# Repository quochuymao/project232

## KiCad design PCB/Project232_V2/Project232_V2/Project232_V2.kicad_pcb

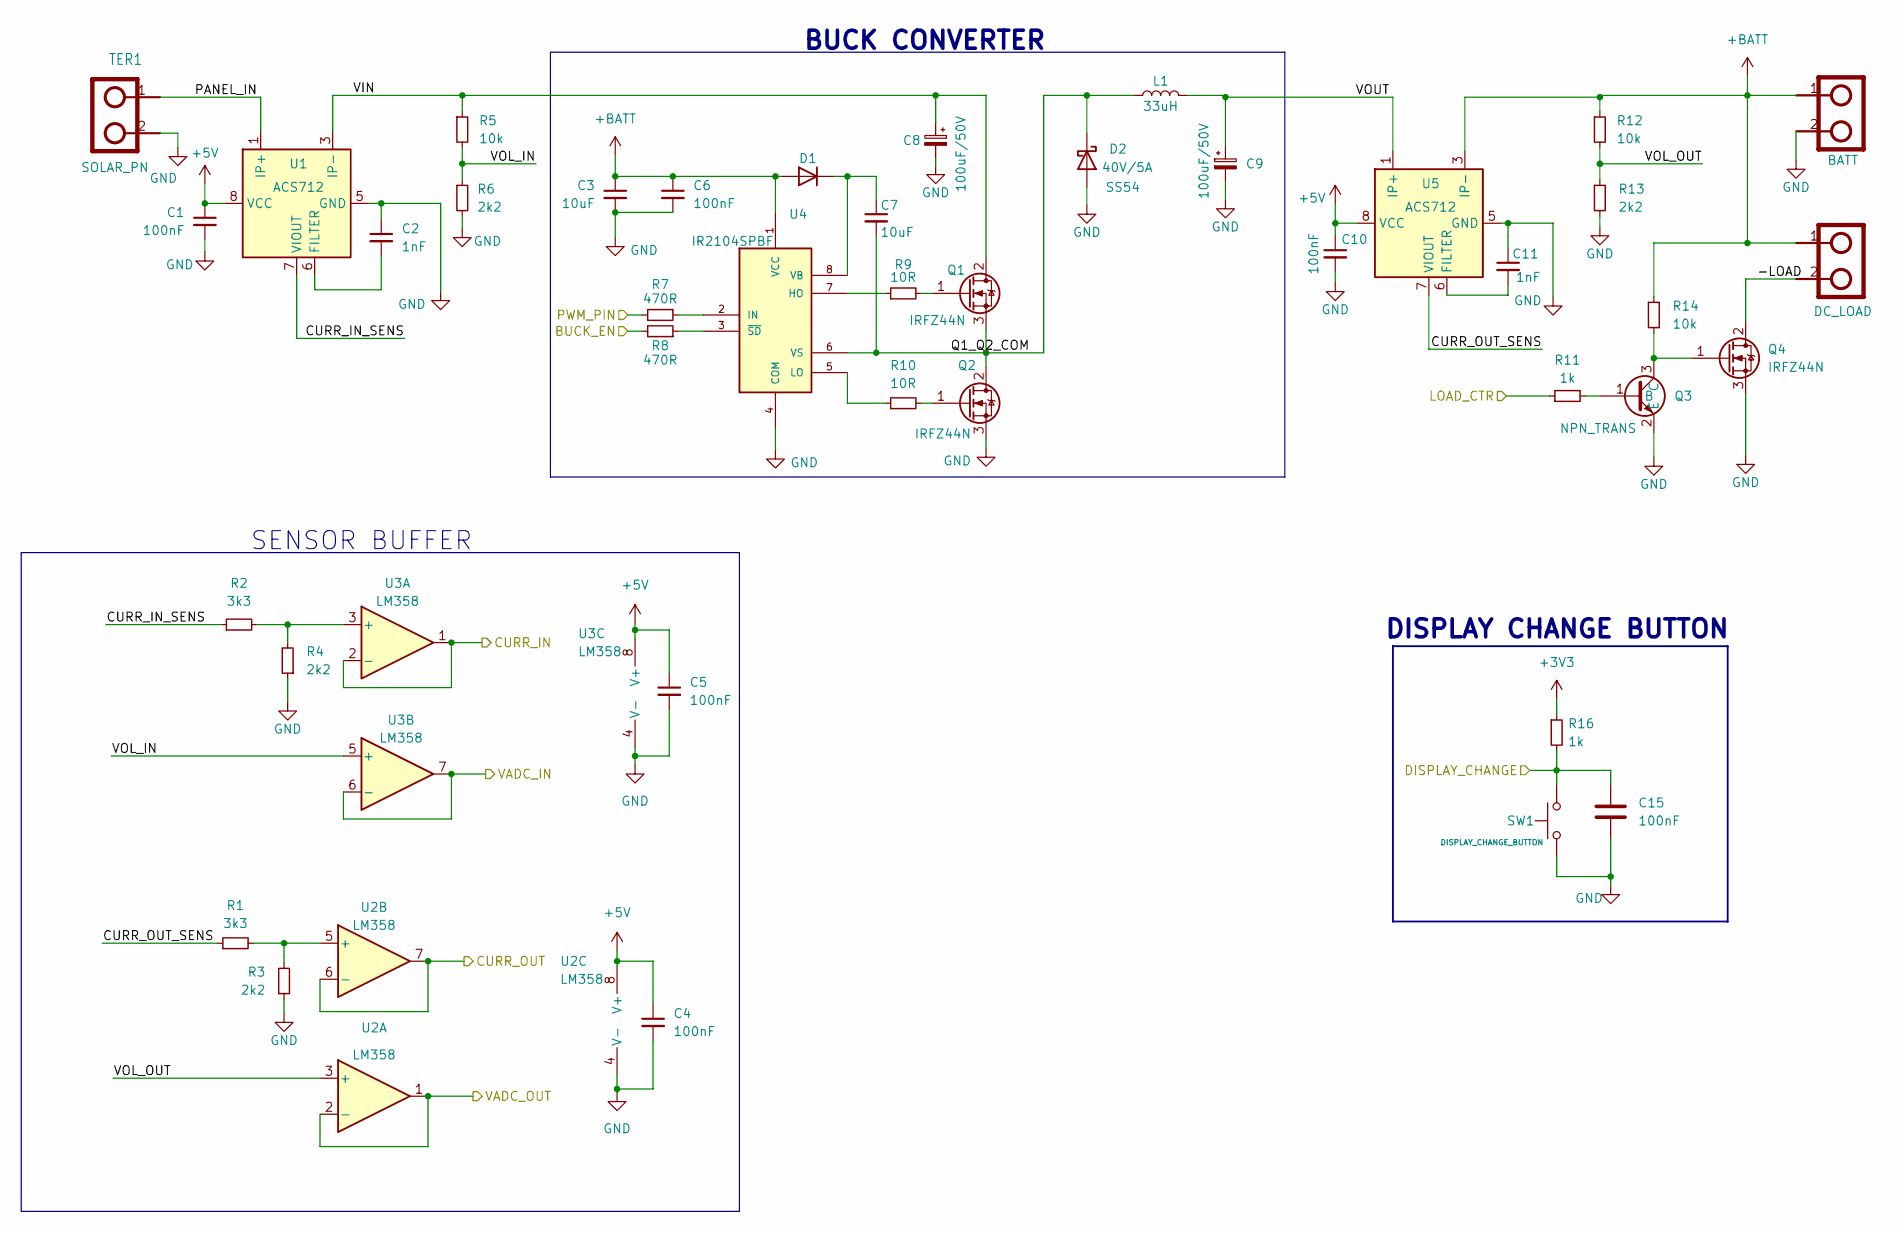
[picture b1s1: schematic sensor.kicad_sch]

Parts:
C1, C4, C5, C6, C10, C15: 100nF; C_0805_2012Metric
C2, C11: 1nF; C_0805_2012Metric
C3, C7: 10uF; C_0805_2012Metric
C8, C9: 100uF/50V; CP_Elec_8x10.5
D1: 1N5819W; D_SOD-123
D2: 40V/5A; D_SMC
L1: 33uH; Inductor_33uH_5A_THT
Q1, Q2, Q4: IRFZ44N; TO-220-3_Vertical
Q3: NPN_TRANS; SOT-23
R1, R2: 3k3; R_0603_1608Metric
R3, R4, R6, R13: 2k2; R_0603_1608Metric
R5, R12, R14: 10k; R_0603_1608Metric
R7, R8: 470R; R_0603_1608Metric
R9, R10: 10R; R_0603_1608Metric
R11, R16: 1k; R_0603_1608Metric
SW1: DISPLAY_CHANGE_BUTTON; Button_3x6_SMD
TER1: SOLAR_PN; TerminalBlock_bornier-2_P5.08mm
TER2: BATT; TerminalBlock_bornier-2_P5.08mm
TER3: DC_LOAD; TerminalBlock_bornier-2_P5.08mm
U1, U5: ACS712; SOIC-8_3.9x4.9mm_P1.27mm
U2, U3: LM358; SOIC-8_3.9x4.9mm_P1.27mm
U4: IR2104SPBF; SOIC127P600X175-8N; MPN IR2104SPBF

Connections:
+3V3: R16.1; also elsewhere on the board
+5V: C1.1, C4.1, C5.1, C10.1, U1.8 (VCC), U2.8 (V+), U3.8 (V+), U5.8 (VCC); also elsewhere on the board
+BATT: C3.1, C6.1, D1.2 (A), R12.1, R14.1, TER2.1, TER3.1, U4.1 (VCC), U5.3 (IP-), U5.4 (IP-); also elsewhere on the board
/MCU/BUCK_EN: R8.2; also elsewhere on the board
/MCU/CURR_IN: U3.1, U3.2 (-); also elsewhere on the board
/MCU/CURR_OUT: U2.6 (-), U2.7; also elsewhere on the board
/MCU/DISPLAY_CHANGE: C15.1, R16.2, SW1.1; also elsewhere on the board
/MCU/LOAD_CTR: R11.1; also elsewhere on the board
/MCU/PWM_PIN: R7.2; also elsewhere on the board
/MCU/VADC_IN: U3.6 (-), U3.7; also elsewhere on the board
/MCU/VADC_OUT: U2.1, U2.2 (-); also elsewhere on the board
/Sensor/-LOAD: Q4.2 (D), TER3.2
/Sensor/CURR_IN_SENS: R2.1, U1.7 (VIOUT)
/Sensor/CURR_OUT_SENS: R1.1, U5.7 (VIOUT)
/Sensor/PANEL_IN: TER1.1, U1.1 (IP+), U1.2 (IP+)
/Sensor/Q1_Q2_COM: C7.2, D2.1 (K), L1.1, Q1.3 (S), Q2.2 (D), U4.6 (VS)
/Sensor/VIN: C8.1, Q1.2 (D), R5.1, U1.3 (IP-), U1.4 (IP-)
/Sensor/VOL_IN: R5.2, R6.1, U3.5 (+)
/Sensor/VOL_OUT: R12.2, R13.1, U2.3 (+)
/Sensor/VOUT: C9.1, L1.2, U5.1 (IP+), U5.2 (IP+)
GND: C1.2, C2.1, C3.2, C4.2, C5.2, C6.2, C8.2, C9.2, C10.2, C11.1, C15.2, D2.2 (A), Q2.3 (S), Q3.2 (E), Q4.3 (S), R3.1, R4.1, R6.2, R13.2, SW1.2, TER1.2, TER2.2, U1.5 (GND), U2.4 (V-), U3.4 (V-), U4.4 (COM), U5.5 (GND); also elsewhere on the board
unnamed: C7.1, D1.1 (K), U4.8 (VB)
unnamed: Q1.1 (G), R9.2
unnamed: Q2.1 (G), R10.2
unnamed: Q3.1 (B), R11.2
unnamed: Q3.3 (C), Q4.1 (G), R14.2
unnamed: C2.2, U1.6 (FILTER)
unnamed: R1.2, R3.2, U2.5 (+)
unnamed: R2.2, R4.2, U3.3 (+)
unnamed: R9.1, U4.7 (HO)
unnamed: R7.1, U4.2 (IN)
unnamed: R10.1, U4.5 (LO)
unnamed: R8.1, U4.3 (~SD)
unnamed: C11.2, U5.6 (FILTER)

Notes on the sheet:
BUCK CONVERTER
SENSOR BUFFER
DISPLAY CHANGE BUTTON

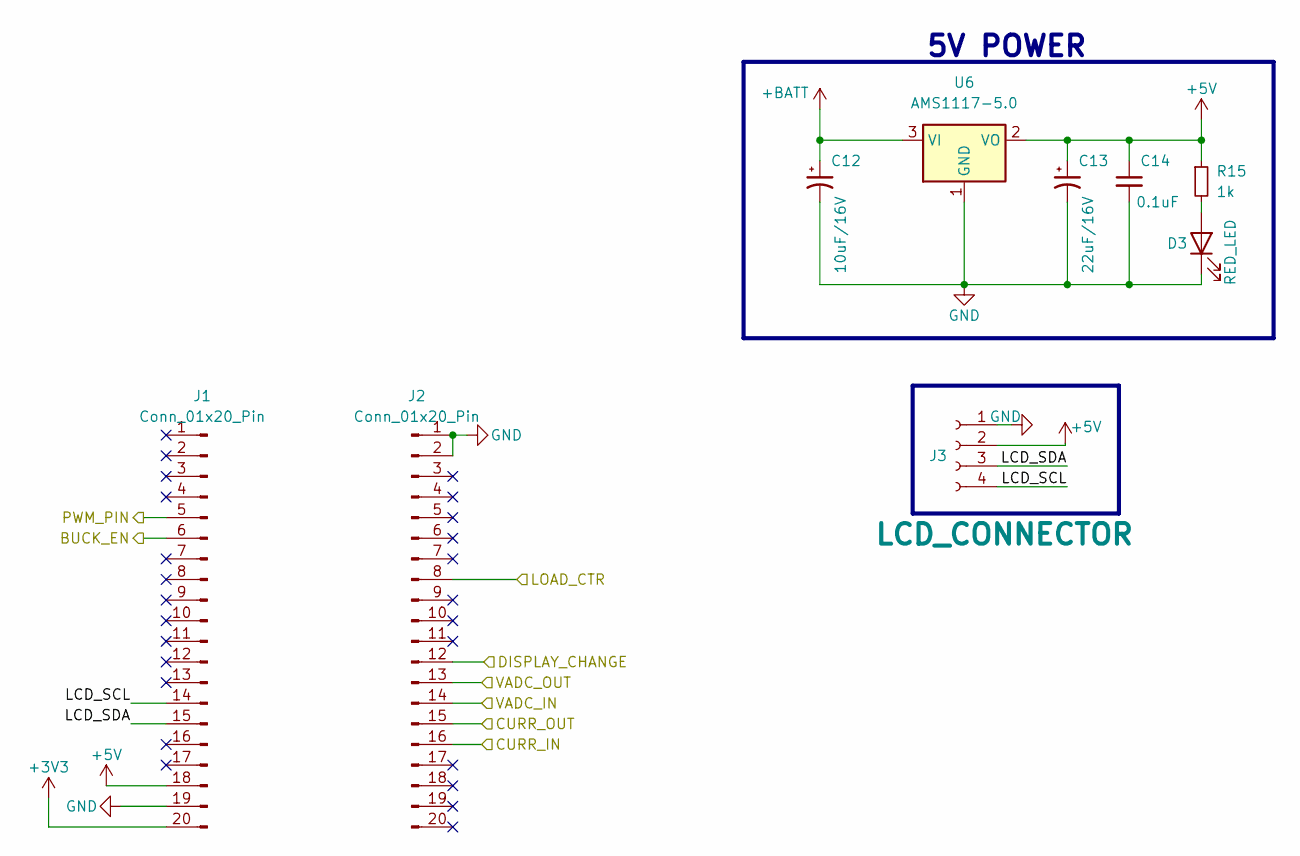
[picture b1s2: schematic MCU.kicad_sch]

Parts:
C12: 10uF/16V; CP_Elec_4x5.4
C13: 22uF/16V; CP_Elec_4x5.4
C14: 0.1uF; C_0805_2012Metric
D3: RED_LED; LED_0805_2012Metric
J1, J2: Conn_01x20_Pin; PinHeader_1x20_P2.54mm_Vertical
J3: LCD_CONNECTOR; PinHeader_1x04_P2.54mm_Vertical
R15: 1k; R_0603_1608Metric
U6: AMS1117-5.0; SOT-223-3_TabPin2

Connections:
+3V3: J1.20; also elsewhere on the board
+5V: C13.1, C14.1, J1.18, J3.2, R15.1, U6.2 (VO); also elsewhere on the board
+BATT: C12.1, U6.3 (VI); also elsewhere on the board
/MCU/BUCK_EN: J1.6; also elsewhere on the board
/MCU/CURR_IN: J2.16; also elsewhere on the board
/MCU/CURR_OUT: J2.15; also elsewhere on the board
/MCU/DISPLAY_CHANGE: J2.12; also elsewhere on the board
/MCU/LCD_SCL: J1.14, J3.4
/MCU/LCD_SDA: J1.15, J3.3
/MCU/LOAD_CTR: J2.8; also elsewhere on the board
/MCU/PWM_PIN: J1.5; also elsewhere on the board
/MCU/VADC_IN: J2.14; also elsewhere on the board
/MCU/VADC_OUT: J2.13; also elsewhere on the board
GND: C12.2, C13.2, C14.2, D3.1 (K), J1.19, J2.1, J2.2, J3.1, U6.1 (GND); also elsewhere on the board
unnamed: D3.2 (A), R15.2

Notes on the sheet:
5V POWER

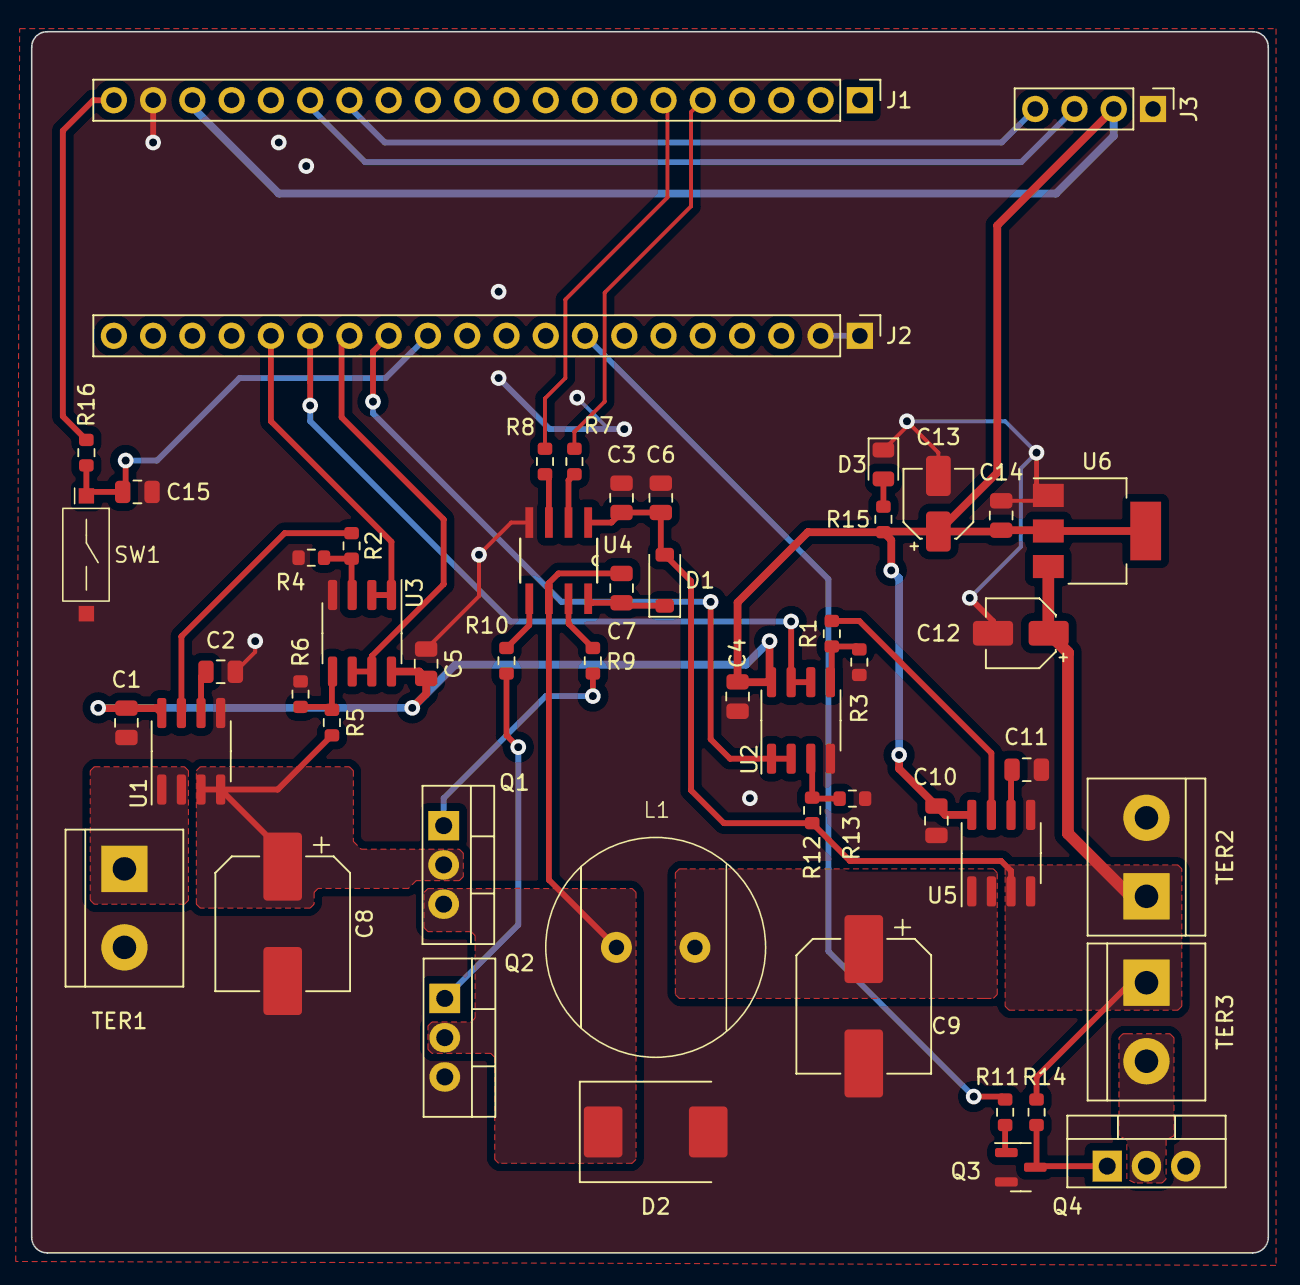
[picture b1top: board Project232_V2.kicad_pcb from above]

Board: 2 copper layers, 80.0 x 79.0 mm, 52 parts (0 on the bottom side), 37 nets.

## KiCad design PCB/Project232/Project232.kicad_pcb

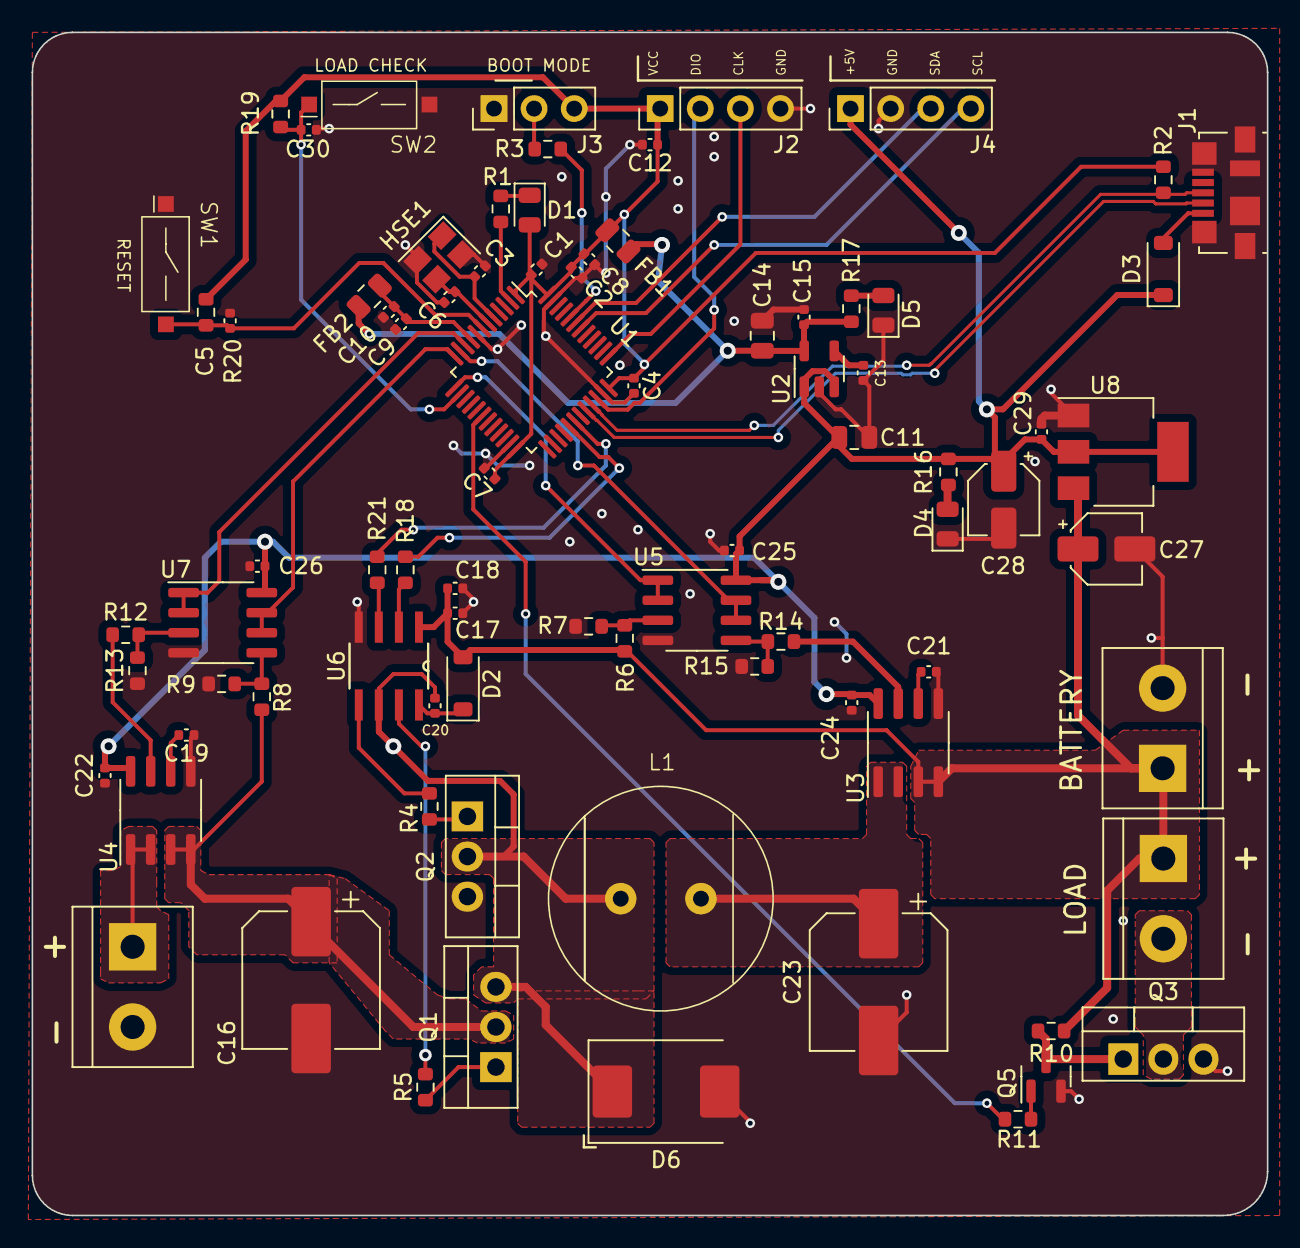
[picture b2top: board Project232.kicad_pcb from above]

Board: 2 copper layers, 78.2 x 74.9 mm, 82 parts (0 on the bottom side), 53 nets.

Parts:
C1: 4.7uF; C_0402_1005Metric
C2, C4, C7, C8, C9, C12, C18, C22, C24, C25, C26, C30: 100nF; C_0402_1005Metric
C3, C6: 15pF; C_0402_1005Metric
C5: 4.7nF; C_0402_1005Metric
C10: 1uF; C_0402_1005Metric
C11: 10uF/16V; C_0805_2012Metric
C13, C15, C29: 0.1uF; C_0402_1005Metric
C14: 22uF/16V; C_0805_2012Metric
C16, C23: 100uF/50V; CP_Elec_8x10.5
C17, C20: 10uF; C_0402_1005Metric
C19, C21: 1nF; C_0402_1005Metric
C27: 10uF/16V; CP_Elec_4x5.4
C28: 22uF/16V; CP_Elec_4x5.4
D1: RED_LED; LED_0805_2012Metric
D2: 1N5819W; D_SOD-123
D3: B120-E3; D_SOD-123
D4, D5: LED; LED_0805_2012Metric
D6: 40V/5A; D_SMC
FB1, FB2: 0805; C_0805_2012Metric
HSE1: 8MHz; Crystal_SMD_3225-4Pin_3.2x2.5mm
J1: USB_B_Micro; USB_Micro-B_Molex_47346-0001
J2: SPI CONNECTOR; PinHeader_1x04_P2.54mm_Vertical
J3: BOOT MODE; PinHeader_1x03_P2.54mm_Vertical
J4: LCD_CONNECTOR; PinHeader_1x04_P2.54mm_Vertical
L1: 33uH; Inductor_33uH_5A_THT
Q1, Q2, Q3: IRF3205; TO-220-3_Vertical
Q5: SOT-23
R1: 150R; R_0603_1608Metric
R2: 4k7; R_0603_1608Metric
R3, R6, R8, R10, R20: 10k; R_0603_1608Metric
R4, R5: 10R; R_0603_1608Metric
R7, R9, R13, R15: 2k2; R_0603_1608Metric
R11, R16, R17, R19: 1k; R_0603_1608Metric
R12, R14: 3k3; R_0603_1608Metric
R18, R21: 470R; R_0603_1608Metric
SW1: RESET; Button_3x6_SMD
SW2: LOAD_CHECK_BUTTON; Button_3x6_SMD
TER1: SOLAR_PN; TerminalBlock_bornier-2_P5.08mm
TER2: BATT; TerminalBlock_bornier-2_P5.08mm
TER3: DC_LOAD; TerminalBlock_bornier-2_P5.08mm
U1: STM32F103C8T6; LQFP-48_7x7mm_P0.5mm
U2: MIC5205-3.3YM5; SOT-23-5
U3, U4: ACS712; SOIC-8_3.9x4.9mm_P1.27mm
U5, U7: LM358; SOIC-8_3.9x4.9mm_P1.27mm
U6: IR2104SPBF; SOIC127P600X175-8N
U8: AMS1117-5.0; SOT-223-3_TabPin2

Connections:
+5V: C11.1, C22.1, C24.1, C25.1, C26.1, C28.1, C29.1, D3.1 (K), J4.1, R16.1, U2.1 (IN), U2.3 (EN), U3.8 (VCC), U4.8 (VCC), U5.8 (V+), U7.8 (V+), U8.2 (VO)
+BATT: C17.1, C18.1, C27.1, D2.2 (A), R6.1, R10.1, TER2.1, TER3.1, U3.3 (IP-), U3.4 (IP-), U6.1 (VCC), U8.3 (VI)
/MCU/BOOT0: R3.2, U1.44 (BOOT0)
/MCU/BUCK_EN: R21.2, U1.30 (PA9)
/MCU/CURR_IN: U1.10 (PA0), U7.1, U7.2 (-)
/MCU/CURR_OUT: U1.11 (PA1), U5.6 (-), U5.7
/MCU/DEBUG_LED: R1.1, U1.2 (PC13)
/MCU/HSE_IN: C3.1, HSE1.1, U1.5 (PD0)
/MCU/HSE_OUT: C6.1, HSE1.3, U1.6 (PD1)
/MCU/LCD_SCL: J4.4, U1.42 (PB6)
/MCU/LCD_SDA: J4.3, U1.43 (PB7)
/MCU/LOAD_CHECK: C30.1, R19.2, SW2.1, U1.14 (PA4)
/MCU/LOAD_CTR: R11.1, U1.18 (PB0)
/MCU/NRST: C5.1, R20.1, SW1.2, U1.7 (NRST)
/MCU/PWM_PIN: R18.2, U1.29 (PA8)
/MCU/SWCLK: J2.3, U1.37 (PA14)
/MCU/SWDIO: J2.2, U1.34 (PA13)
/MCU/USB+: J1.3 (D+), R2.2, U1.33 (PA12)
/MCU/USB-: J1.2 (D-), U1.32 (PA11)
/MCU/VADC_IN: U1.12 (PA2), U7.6 (-), U7.7
/MCU/VADC_OUT: U1.13 (PA3), U5.1, U5.2 (-)
/Sens/-LOAD: Q3.2 (D), TER3.2
/Sens/CURR_IN_SENS: R12.1, U4.7 (VIOUT)
/Sens/CURR_OUT_SENS: R14.1, U3.7 (VIOUT)
/Sens/PANEL_IN: TER1.1, U4.1 (IP+), U4.2 (IP+)
/Sens/Q1_Q2_COM: C20.2, D6.1 (K), L1.1, Q1.3 (S), Q2.2 (D), U6.6 (VS)
/Sens/VIN: C16.1, Q1.2 (D), R8.1, U4.3 (IP-), U4.4 (IP-)
/Sens/VOL_IN: R8.2, R9.1, U7.5 (+)
/Sens/VOL_OUT: R6.2, R7.1, U5.3 (+)
/Sens/VOUT: C23.1, L1.2, U3.1 (IP+), U3.2 (IP+)
GND: C1.2, C2.2, C3.2, C4.2, C5.2, C6.2, C7.2, C8.2, C9.2, C10.2, C11.2, C12.2, C13.2, C14.2, C15.2, C16.2, C17.2, C18.2, C19.1, C21.1, C22.2, C23.2, C24.2, C25.2, C26.2, C27.2, C28.2, C29.2, C30.2, D4.1 (K), D5.1 (K), D6.2 (A), HSE1.2, HSE1.4, J1.5 (GND), J1.6 (Shield), J2.4, J3.1, J4.2, Q2.3 (S), Q3.3 (S), Q5.2 (E), R7.2, R9.2, R13.1, R15.1, SW1.1, SW2.2, TER1.2, TER2.2, U1.8 (VSSA), U1.23 (VSS), U1.35 (VSS), U1.47 (VSS), U2.2 (GND), U3.5 (GND), U4.5 (GND), U5.4 (V-), U6.4 (COM), U7.4 (V-), U8.1 (GND)
unnamed: D1.1 (K), R1.2
unnamed: C20.1, D2.1 (K), U6.8 (VB)
unnamed: D3.2 (A), J1.1 (VBUS)
unnamed: D4.2 (A), R16.2
unnamed: D5.2 (A), R17.2
unnamed: J3.2, R3.1
unnamed: Q1.1 (G), R5.2
unnamed: Q2.1 (G), R4.2
unnamed: Q3.1 (G), Q5.3 (C), R10.2
unnamed: Q5.1 (B), R11.2
unnamed: C13.1, U2.4 (BP)
unnamed: C14.1, C15.1, FB1.2, FB2.2, R17.1, U2.5 (OUT)
unnamed: C21.2, U3.6 (FILTER)
unnamed: C19.2, U4.6 (FILTER)
unnamed: R14.2, R15.2, U5.5 (+)
unnamed: R5.1, U6.7 (HO)
unnamed: R18.1, U6.2 (IN)
unnamed: R4.1, U6.5 (LO)
unnamed: R21.1, U6.3 (~SD)
unnamed: R12.2, R13.2, U7.3 (+)
VCC: C1.1, C2.1, C4.1, C7.1, C8.1, C12.1, D1.2 (A), FB1.1, J2.1, J3.3, R2.1, R19.1, R20.2, U1.1 (VBAT), U1.24 (VDD), U1.36 (VDD), U1.48 (VDD)
VDDA: C9.1, C10.1, FB2.1, U1.9 (VDDA)

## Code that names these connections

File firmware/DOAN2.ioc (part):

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Mcu.Name=STM32F103C(8-B)Tx
Mcu.Package=LQFP48
Mcu.UserName=STM32F103C8Tx
PA0-WKUP.GPIOParameters=GPIO_Label
PA0-WKUP.GPIO_Label=CURRENT_IN
PA0-WKUP.Signal=ADCx_IN0
PA1.GPIOParameters=GPIO_Label
PA1.GPIO_Label=CURRENT_OUT
PA1.Signal=ADCx_IN1
PA11.Mode=Device
PA11.Signal=USB_DM
PA12.Mode=Device
PA12.Signal=USB_DP
PA13.Mode=Serial_Wire
PA13.Signal=SYS_JTMS-SWDIO
PA14.Mode=Serial_Wire
PA14.Signal=SYS_JTCK-SWCLK
PA2.GPIOParameters=GPIO_Label
PA2.GPIO_Label=VOLTAGE_IN
PA2.Signal=ADCx_IN2
PA3.GPIOParameters=GPIO_Label
PA3.GPIO_Label=VOLTAGE_OUT
PA3.Signal=ADCx_IN3
PA4.GPIOParameters=GPIO_PuPd,GPIO_Label,GPIO_ModeDefaultEXTI
PA4.GPIO_Label=CHANGE_DISPLAY
PA4.GPIO_ModeDefaultEXTI=GPIO_MODE_IT_FALLING
PA4.GPIO_PuPd=GPIO_PULLUP
PA4.Signal=GPXTI4
PA5.Signal=ADCx_IN5
PA8.GPIOParameters=GPIO_Label
PA8.GPIO_Label=PWM_OUT
PA8.Signal=S_TIM1_CH1
PA9.GPIOParameters=GPIO_Label
PA9.GPIO_Label=BUCK_EN
PA9.Signal=GPIO_Output
PB0.GPIOParameters=GPIO_Label
PB0.GPIO_Label=LOAD_CTR
PB0.Signal=GPIO_Output
PB6.Mode=I2C
PB6.Signal=I2C1_SCL
PB7.Mode=I2C
PB7.Signal=I2C1_SDA
PC13-TAMPER-RTC.GPIOParameters=GPIO_Label
PC13-TAMPER-RTC.GPIO_Label=TEST
PC13-TAMPER-RTC.Signal=GPIO_Output
PD0-OSC_IN.Mode=HSE-External-Oscillator
PD0-OSC_IN.Signal=RCC_OSC_IN
PD1-OSC_OUT.Mode=HSE-External-Oscillator
PD1-OSC_OUT.Signal=RCC_OSC_OUT
RCC.SYSCLKFreq_VALUE=48000000
RCC.SYSCLKSource=RCC_SYSCLKSOURCE_PLLCLK
board=custom

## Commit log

2024-04-10 fist commit
2024-04-10 adding hardware file
2024-04-10 update firmware
2024-04-10 adding datasheet file
2024-04-19 update test board and docs
2024-04-22 update PIN in firmware
2024-04-25 add firmware_API_docs
2024-05-08 Update PCB
2024-05-08 update LCD and ADC function
2024-05-08 update GPIO, PWM function
2024-05-08 add API docs for STM32F103C8T6
2024-05-11 add LCD
2024-05-11 update gerber files
2024-05-11 fix PWM fucntion
2024-05-11 update PWM fucntion
2024-05-11 add docs function
2024-05-12 update code for main - project
2024-05-12 update firmware docs
2024-05-14 conflict fix
2024-05-15 update PCB Board V2
2024-05-16 commmit to push
2024-05-16 test PWM
2024-05-16 test lcd
2024-05-16 update LCD function
2024-05-16 push to pull
2024-05-16 update main
2024-05-23 update flowchart for firmware
2024-05-30 update 30/05/2024
2024-05-30 update code
2024-05-30 update 31/05
2024-06-02 update firmware files
